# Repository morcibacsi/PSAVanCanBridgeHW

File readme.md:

# PSA VAN-CAN protocol bridge (hardware)

### What is it ?
This is the hardware needed for my [PSA CAN protocol bridge][psacanbridge] and [PSA VAN-CAN protocol bridge][psavancanbridge] software.

It was designed using KiCad 7.0.6 as a standalone board with an ESP32-WROOM-32 MCU.

### v1.5

:warning: **IF YOU ARE USING THE BOARD AS A VAN-CAN BOARD THEN BE AWARE THAT THE VAN DATA LINES HAVE BEEN SWAPPED IN THIS VERSION COMPARED TO THE PREVIOUS ONES. DATA LINE IS ON PIN 6 AND DATAB LINE IS ON PIN 5. ON PREVIOUS VERSIONS IT WAS THE OTHER WAY AROUND. SO YOU NEED TO SWAP THOSE WIRES ON YOUR PATCH LEAD IF YOU ARE UPGRADING FROM A PREVIOUS VERSION.**

It won't damage the board or your car, it just won't work if you don't swap the wires.

### Custom SPI shield

To have the flexibility to use either a MCP2515 or a TSS463 I designed a small custom PCB which can be manufactured with castellated holes and can be soldered to the back of this board. This is how it looks like. The design files for this PCB can be found on its own [repository][vancanspishield].

#### VAN-CAN bridge

To use it as a VAN-CAN bridge without the need for a custom SPI shield with the TSS463 you need to close the jumper marked with red rectangle on the front (1). This way the ESP32 will write directly to the VAN bus. You also need to close the jumper marked with red rectangle on the back (2) of the board to 3V3 so the CAN transceiver uses 3.3V logic levels.

If you would like to use the SPI shield with the TSS463 the jumper marked with red rectangle on the back (2) must be closed to 5V.

#### CAN-CAN bridge

To use it as a CAN-CAN bridge you need to populate the SPI shield with a MCP2515 and the jumper marked with red rectangle on the back (2) must be closed to 5V.

### Programming the board

The board can be programmed using the ESP32's UART0 for which you need a USB to serial adapter like on the picture below (or a similar one). As the ESP32 is a 3.3V device you need to make sure that the adapter is also 3.3V compatible.
The pins needed for programming are marked with orange rectangles on the front of the board on the picture below. Depending on the adapter you have you might need to cross connect the TX and RX pins.

You need to hold the BOOT button and press the RESET button to enter programming mode. I usually keep holding the BOOT button until the programming starts. After programming is done you can press the RESET button to restart the board.

💡 **Make sure you don't connect 5V and 12V at the same time to the board**

### Schema

### PCB

### Assembly

The board was designed to be as compact as possible, so I suggest to send the manufacturing files to JLCPCB and order with assembly service. But in order to have a working board some soldering is also needed. You can find the necessary components in the next section.

I bought a [DS3231 real time clock module for Raspberry Pi][DS3231] and disassembled that and placed its parts to J1 and U2.

The board dimensions were designed to fit a [70 x 45 x 18mm case][enclosure].

### BOM

I listed only those which aren't populated by the assembly company.

|Designator|Value         |Package                                         |
|----------|------------|------------------------------------------------|
|U8        |ESP32-WROOM-32      |     |
|J1        |Coin battery for DS3231      |     |
|U2        |DS3231      |SOIC-16W_7.5x10.3mm_P1.27mm     |
|C7        |100uF       |Capacitor_THT:CP_Radial_D6.3mm_P2.50mm     |
|C10       |220uF       |Capacitor_THT:CP_Radial_D6.3mm_P2.50mm     |

The connector for the power and signal wires is a JST-XH6 2.54 mm

The full BOM is in the production folder as a csv.

[vancanspishield]: https://github.com/morcibacsi/VanCanSpiShield
[psacanbridge]: https://github.com/morcibacsi/PSACANBridge
[psavancanbridge]: https://github.com/morcibacsi/PSAVANCANBridge
[DS3231]: https://www.aliexpress.com/item/1005006116699524.html
[enclosure]: https://www.aliexpress.com/item/1005005467281776.html

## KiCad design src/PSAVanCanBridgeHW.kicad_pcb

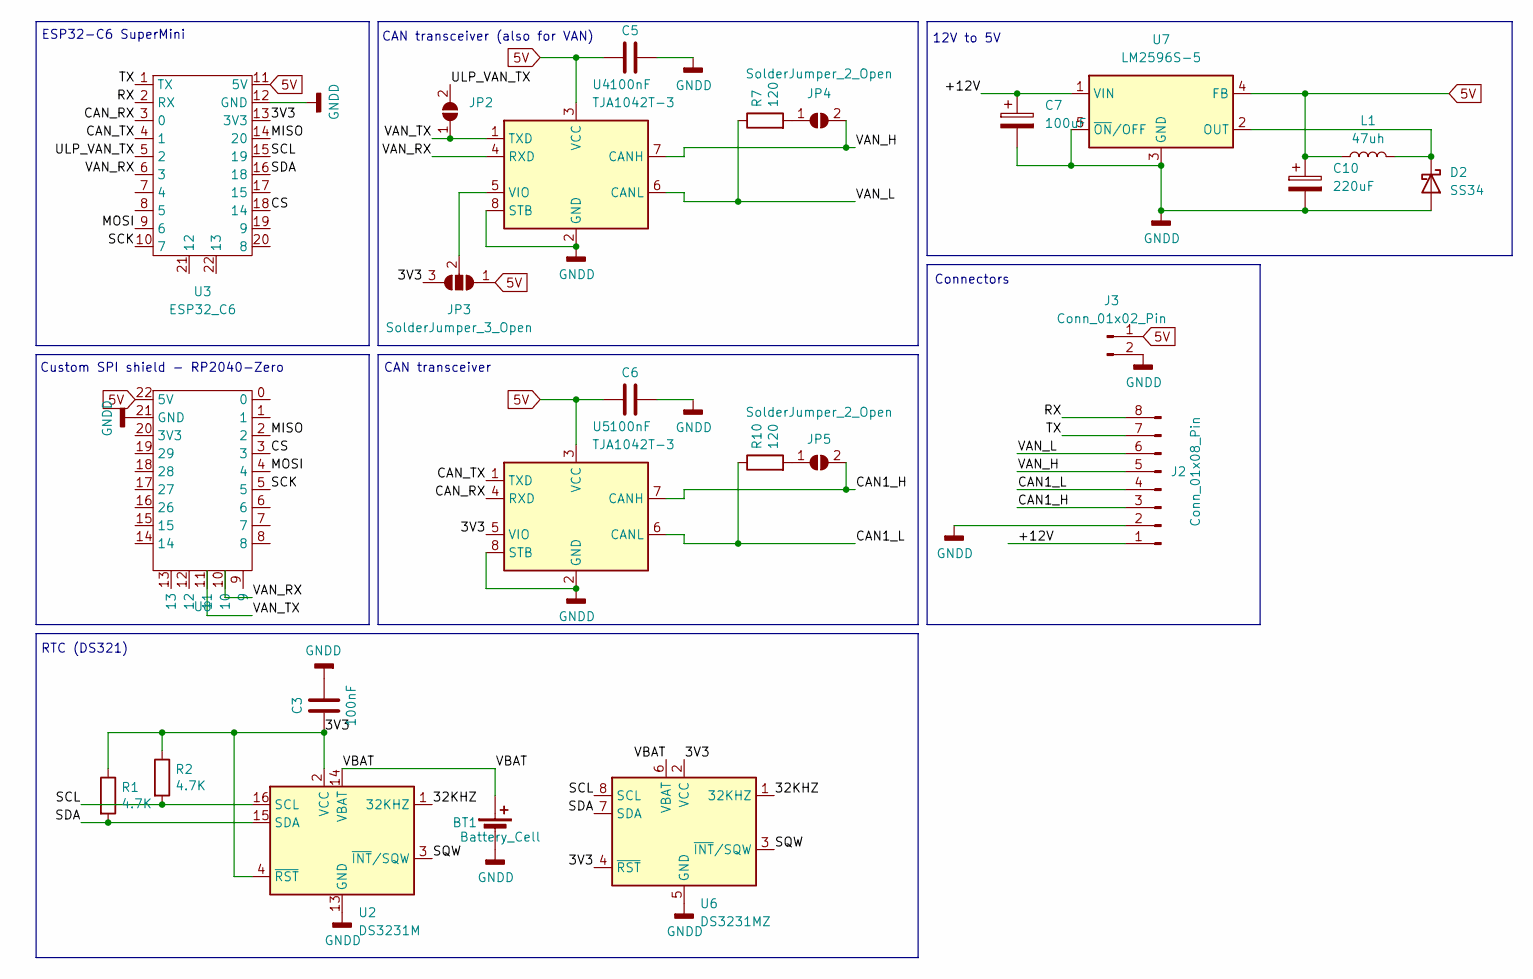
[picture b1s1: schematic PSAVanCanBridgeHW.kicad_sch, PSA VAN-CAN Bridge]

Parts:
BT1: Battery_Cell; BatteryHolder_Keystone_3000_1x12mm
C3, C5, C6: 100nF; C_0603_1608Metric_Pad1.08x0.95mm_HandSolder; MPN CC0603KRX7R9BB104; LCSC C14663
C7: 100uF; CP_Radial_D6.3mm_P2.50mm
C10: 220uF; CP_Radial_D6.3mm_P2.50mm
D2: SS34; D_SMA; MPN SS34; LCSC C7420365
J2: Conn_01x08_Pin; JST_EH_S8B-EH_1x08_P2.50mm_Horizontal
J3: Conn_01x02_Pin; PinHeader_1x02_P2.54mm_Vertical
JP2, JP4, JP5: SolderJumper_2_Open; SolderJumper-2_P1.3mm_Open_Pad1.0x1.5mm
JP3: SolderJumper_3_Open; SolderJumper-3_P1.3mm_Open_Pad1.0x1.5mm_NumberLabels
L1: 47uh; L_12x12mm_H8mm; MPN CDRH127NP-470MC; LCSC C167265
R1, R2: 4.7K; R_0603_1608Metric_Pad0.98x0.95mm_HandSolder; MPN 0603WAF4701T5E; LCSC C23162
R7, R10: 120; R_0603_1608Metric_Pad0.98x0.95mm_HandSolder; MPN 0603WAF1200T5E; LCSC C22787
U2: DS3231M; SOIC-16W_7.5x10.3mm_P1.27mm; JLCPCB Rotation Offset -90
U3: ESP32_C6; ESP32_c6_supermini
U4, U5: TJA1042T-3; SOIC-8_3.9x4.9mm_P1.27mm; MPN TJA1042T/3/1J; LCSC C132227
U6: DS3231MZ; SOIC-8_3.9x4.9mm_P1.27mm; MPN DS3231MZ+TRL; LCSC C37663
U7: LM2596S-5; TO-263-5_TabPin3; MPN LM2596S-5.0(UMW); LCSC C347421
U8: RP2040-Zero

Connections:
5V: C5.2, C6.2, C10.1, J3.1, JP3.1 (A), L1.1, U3.11 (5V), U4.3 (VCC), U5.3 (VCC), U7.4 (FB), U8.22 (5V)
/3V3: C3.2, JP3.3 (B), R1.1, R2.1, U2.2 (VCC), U2.4 (~RST), U3.13 (3V3), U5.5 (VIO), U6.2 (VCC), U6.4 (~RST)
/32KHZ: U2.1 (32KHZ), U6.1 (32KHZ)
/+12V: C7.1, J2.1, U7.1 (VIN)
/CAN1_H: J2.3, JP5.2 (B), U5.7 (CANH)
/CAN1_L: J2.4, R10.1, U5.6 (CANL)
/CAN_RX: U3.3 (0), U5.4 (RXD)
/CAN_TX: U3.4 (1), U5.1 (TXD)
/CS: U3.18 (14), U8.3
/MISO: U3.14 (20), U8.2
/MOSI: U3.9 (6), U8.4
/RX: J2.8, U3.2 (RX)
/SCK: U3.10 (7), U8.5
/SCL: R2.2, U2.16 (SCL), U3.15 (19), U6.8 (SCL)
/SDA: R1.2, U2.15 (SDA), U3.16 (18), U6.7 (SDA)
/SQW: U2.3 (~INT/SQW), U6.3 (~INT/SQW)
/TX: J2.7, U3.1 (TX)
/ULP_VAN_TX: JP2.2 (B), U3.5 (2)
/VAN_H: J2.5, JP4.2 (B), U4.7 (CANH)
/VAN_L: J2.6, R7.1, U4.6 (CANL)
/VAN_RX: U3.6 (3), U4.4 (RXD), U8.10
/VAN_TX: JP2.1 (A), U4.1 (TXD), U8.11
/VBAT: BT1.1 (+), U2.14 (VBAT), U6.6 (VBAT)
GNDD: BT1.2 (-), C3.1, C5.1, C6.1, C7.2, C10.2, D2.2 (A), J2.2, J3.2, U2.5 (GND), U2.6 (GND), U2.7 (GND), U2.8 (GND), U2.9 (GND), U2.10 (GND), U2.11 (GND), U2.12 (GND), U2.13 (GND), U3.12 (GND), U4.2 (GND), U4.8 (STB), U5.2 (GND), U5.8 (STB), U6.5 (GND), U7.3 (GND), U7.5 (~ON/OFF), U8.21 (GND)
unnamed: D2.1 (K), L1.2, U7.2 (OUT)
unnamed: JP3.2 (C), U4.5 (VIO)
unnamed: JP4.1 (A), R7.2
unnamed: JP5.1 (A), R10.2

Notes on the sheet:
RTC (DS321)
Connectors
Custom SPI shield - RP2040-Zero
CAN transceiver
12V to 5V
ESP32-C6 SuperMini
CAN transceiver (also for VAN)

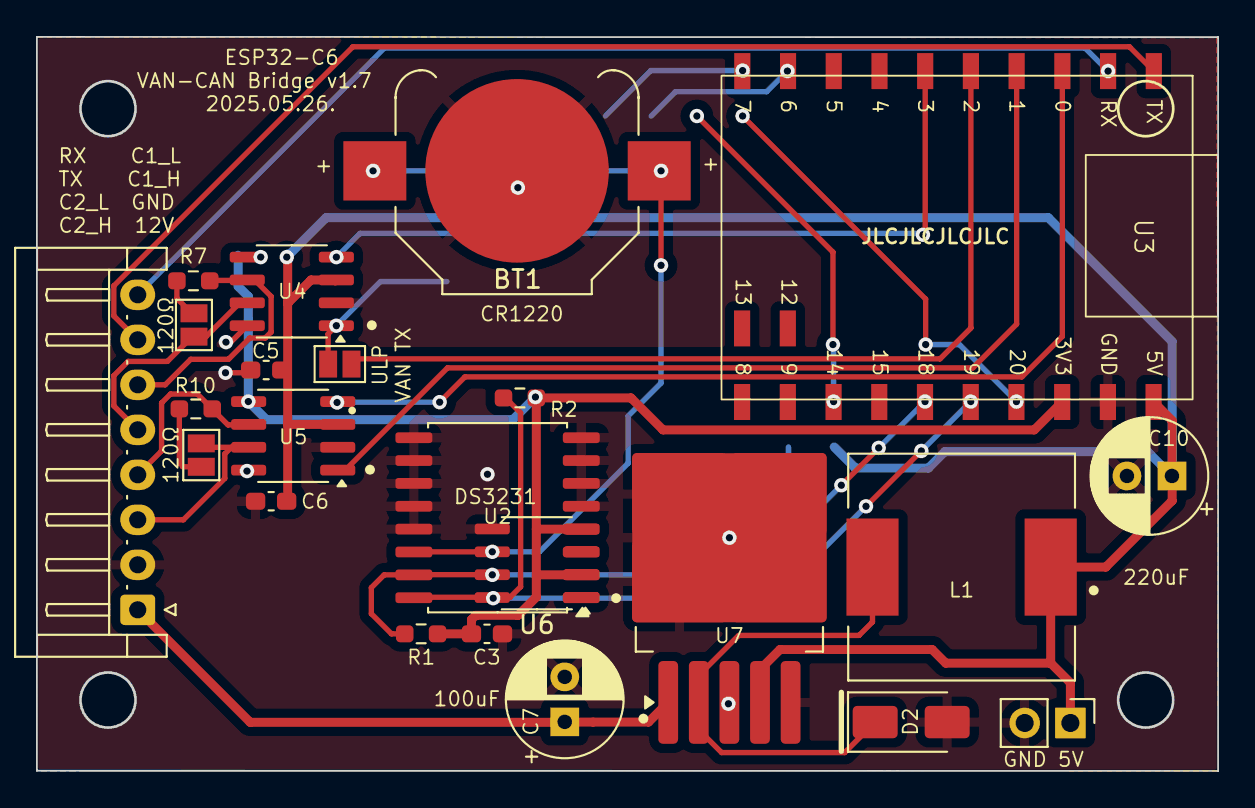
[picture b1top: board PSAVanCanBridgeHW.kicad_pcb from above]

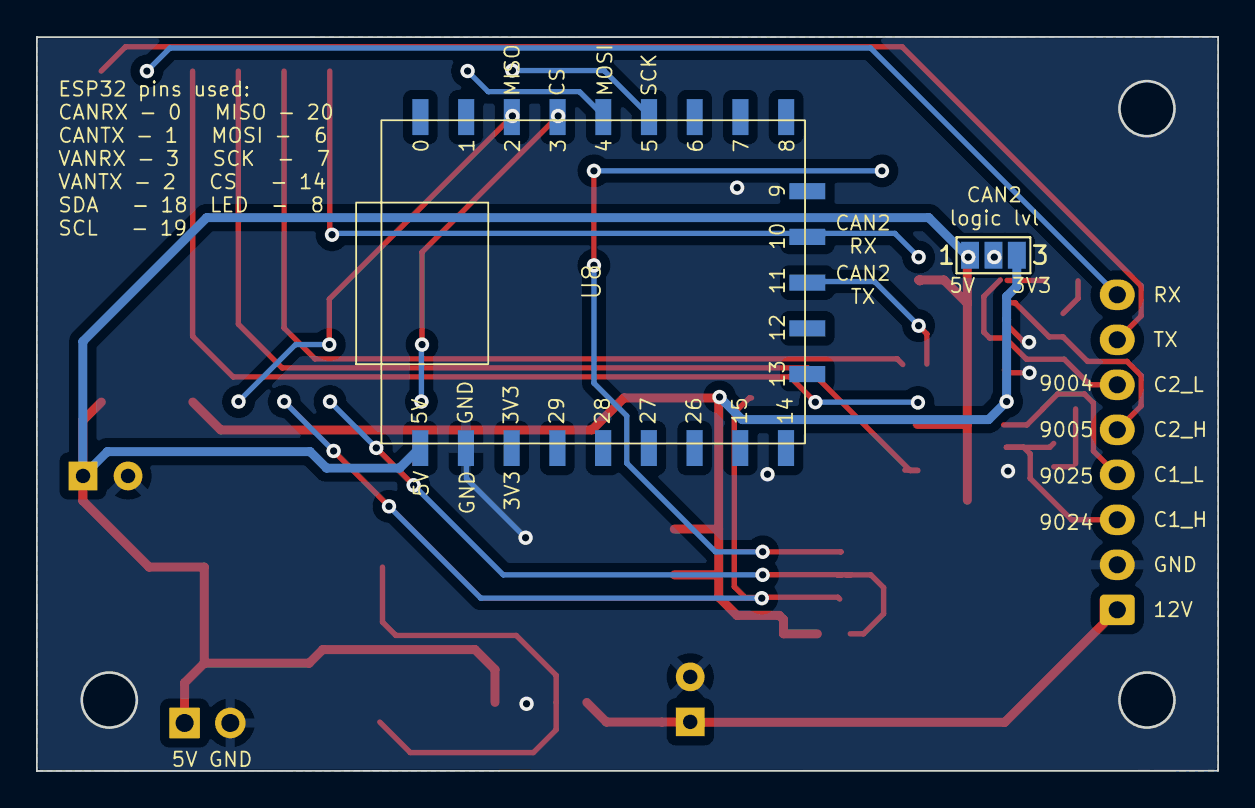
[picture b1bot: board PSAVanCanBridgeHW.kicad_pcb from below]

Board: 2 copper layers, 65.6 x 40.8 mm, 25 parts (2 on the bottom side), 28 nets.

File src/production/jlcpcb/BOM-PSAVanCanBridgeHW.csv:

Comment,Designator,Footprint,LCSC,Quantity
DS3231M,"U2",SOIC-16W_7.5x10.3mm_P1.27mm,C37663,2
DS3231MZ,"U6",SOIC-8_3.9x4.9mm_P1.27mm,C107410,2
TJA1042T-3,"U4,U5",SOIC-8_3.9x4.9mm_P1.27mm,C132227,2
100nF,"C3,C5,C6",C_0603_1608Metric_Pad1.08x0.95mm_HandSolder,C14663,3
47uh,L1,L_12x12mm_H8mm,C167265,1
120,"R10,R7",R_0603_1608Metric_Pad0.98x0.95mm_HandSolder,C22787,2
4.7K,"R1,R2",R_0603_1608Metric_Pad0.98x0.95mm_HandSolder,C23162,2
LM2596S-5,U7,TO-263-5_TabPin3,C347421,1
SS34,D2,D_SMA,C7420365,1
Conn_01x02_Pin,J3,PinHeader_1x02_P2.54mm_Vertical,,1
Battery_Cell,BT1,BatteryHolder_Keystone_3000_1x12mm,,1
220uF,C10,CP_Radial_D6.3mm_P2.50mm,,1
100uF,C7,CP_Radial_D6.3mm_P2.50mm,,1
Conn_01x08_Pin,J2,JST_EH_S8B-EH_1x08_P2.50mm_Horizontal,,1

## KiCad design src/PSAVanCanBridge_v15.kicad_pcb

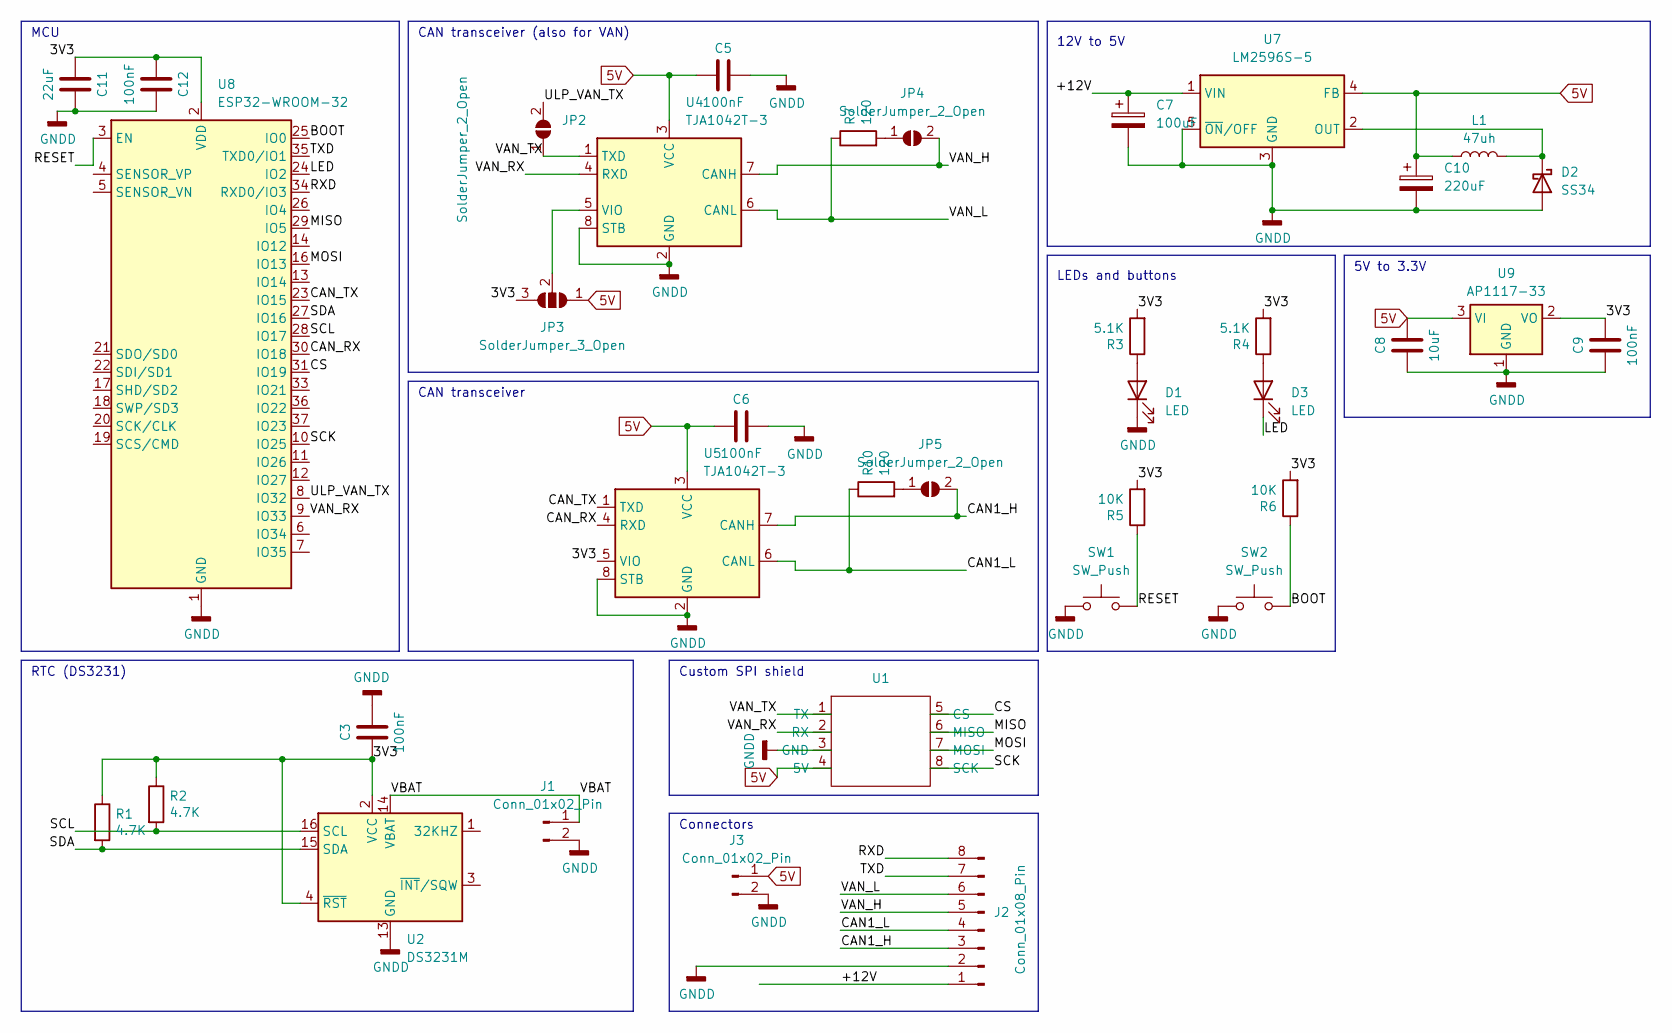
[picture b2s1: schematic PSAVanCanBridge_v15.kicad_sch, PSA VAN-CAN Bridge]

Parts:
C3, C5, C6, C12: 100nF; C_0603_1608Metric_Pad1.08x0.95mm_HandSolder; LCSC C14663
C7: 100uF; CP_Radial_D6.3mm_P2.50mm
C8: 10uF; C_0805_2012Metric_Pad1.18x1.45mm_HandSolder; LCSC C15850
C9: 100nF; C_0805_2012Metric_Pad1.18x1.45mm_HandSolder; LCSC C15850
C10: 220uF; CP_Radial_D6.3mm_P2.50mm
C11: 22uF; C_1206_3216Metric_Pad1.33x1.80mm_HandSolder; LCSC C478862
D1: LED; LED_0603_1608Metric_Pad1.05x0.95mm_HandSolder; LCSC C2286
D2: SS34; D_SMA; LCSC C7420365
D3: LED; LED_0805_2012Metric_Pad1.15x1.40mm_HandSolder; LCSC C2297
J1: Conn_01x02_Pin; DS3231_BatteryHolder
J2: Conn_01x08_Pin; JST_EH_S8B-EH_1x08_P2.50mm_Horizontal
J3: Conn_01x02_Pin; PinHeader_1x02_P2.54mm_Vertical
JP2, JP4, JP5: SolderJumper_2_Open; SolderJumper-2_P1.3mm_Open_Pad1.0x1.5mm
JP3: SolderJumper_3_Open; SolderJumper-3_P1.3mm_Open_Pad1.0x1.5mm_NumberLabels
L1: 47uh; L_12x12mm_H8mm; LCSC C167265
R1, R2: 4.7K; R_0603_1608Metric_Pad0.98x0.95mm_HandSolder; LCSC C25999
R3, R4: 5.1K; R_0603_1608Metric_Pad0.98x0.95mm_HandSolder; LCSC C473622
R5, R6: 10K; R_1206_3216Metric_Pad1.30x1.75mm_HandSolder; LCSC C431903
R7, R10: 120; R_0603_1608Metric_Pad0.98x0.95mm_HandSolder; LCSC C22787
SW1, SW2: SW_Push; SW_Push_1P1T_XKB_TS-1187A; LCSC C318884
U1: SPI_Shield
U2: DS3231M; SOIC-16W_7.5x10.3mm_P1.27mm; JLCPCB Rotation Offset -90
U4, U5: TJA1042T-3; SOIC-8_3.9x4.9mm_P1.27mm; LCSC C132227
U7: LM2596S-5; TO-263-5_TabPin3; LCSC C347421
U8: ESP32-WROOM-32
U9: AP1117-33; SOT-223-3_TabPin2; LCSC C6186

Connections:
5V: C5.2, C6.2, C8.1, C10.1, J3.1, JP3.1 (A), L1.1, U1.4 (5V), U4.3 (VCC), U5.3 (VCC), U7.4 (FB), U9.3 (VI)
/3V3: C3.2, C9.1, C11.2, C12.2, JP3.3 (B), R1.1, R2.1, R3.2, R4.2, R5.2, R6.2, U2.2 (VCC), U2.4 (~RST), U5.5 (VIO), U8.2 (VDD), U9.2 (VO)
/+12V: C7.1, J2.1, U7.1 (VIN)
/BOOT: R6.1, SW2.2, U8.25 (IO0)
/CAN1_H: J2.3, JP5.2 (B), U5.7 (CANH)
/CAN1_L: J2.4, R10.1, U5.6 (CANL)
/CAN_RX: U5.4 (RXD), U8.30 (IO18)
/CAN_TX: U5.1 (TXD), U8.23 (IO15)
/CS: U1.5 (CS), U8.31 (IO19)
/LED: D3.1 (K), U8.24 (IO2)
/MISO: U1.6 (MISO), U8.29 (IO5)
/MOSI: U1.7 (MOSI), U8.16 (IO13)
/RESET: R5.1, SW1.2, U8.3 (EN)
/RXD: J2.8, U8.34 (RXD0/IO3)
/SCK: U1.8 (SCK), U8.10 (IO25)
/SCL: R2.2, U2.16 (SCL), U8.28 (IO17)
/SDA: R1.2, U2.15 (SDA), U8.27 (IO16)
/TXD: J2.7, U8.35 (TXD0/IO1)
/ULP_VAN_TX: JP2.2 (B), U8.8 (IO32)
/VAN_H: J2.5, JP4.2 (B), U4.7 (CANH)
/VAN_L: J2.6, R7.1, U4.6 (CANL)
/VAN_RX: U1.2 (RX), U4.4 (RXD), U8.9 (IO33)
/VAN_TX: JP2.1 (A), U1.1 (TX), U4.1 (TXD)
/VBAT: J1.1, U2.14 (VBAT)
GNDD: C3.1, C5.1, C6.1, C7.2, C8.2, C9.2, C10.2, C11.1, C12.1, D1.1 (K), D2.2 (A), J1.2, J2.2, J3.2, SW1.1, SW2.1, U1.3 (GND), U2.5 (GND), U2.6 (GND), U2.7 (GND), U2.8 (GND), U2.9 (GND), U2.10 (GND), U2.11 (GND), U2.12 (GND), U2.13 (GND), U4.2 (GND), U4.8 (STB), U5.2 (GND), U5.8 (STB), U7.3 (GND), U7.5 (~ON/OFF), U8.1 (GND), U8.15 (GND), U8.38 (GND), U8.39 (GND), U9.1 (GND)
unnamed: D1.2 (A), R3.1
unnamed: D2.1 (K), L1.2, U7.2 (OUT)
unnamed: D3.2 (A), R4.1
unnamed: JP3.2 (C), U4.5 (VIO)
unnamed: JP4.1 (A), R7.2
unnamed: JP5.1 (A), R10.2

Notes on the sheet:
RTC (DS3231)
12V to 5V
Custom SPI shield
CAN transceiver (also for VAN)
LEDs and buttons
Connectors
5V to 3.3V
CAN transceiver
MCU

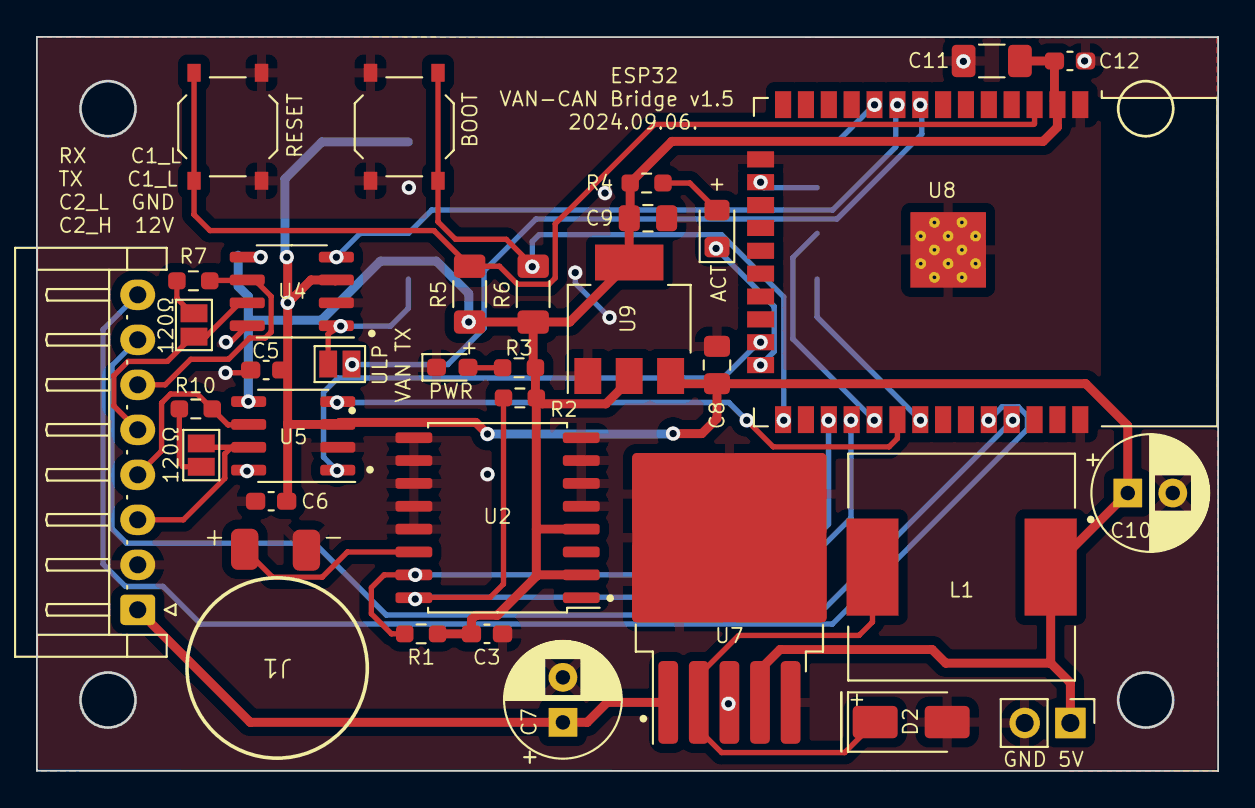
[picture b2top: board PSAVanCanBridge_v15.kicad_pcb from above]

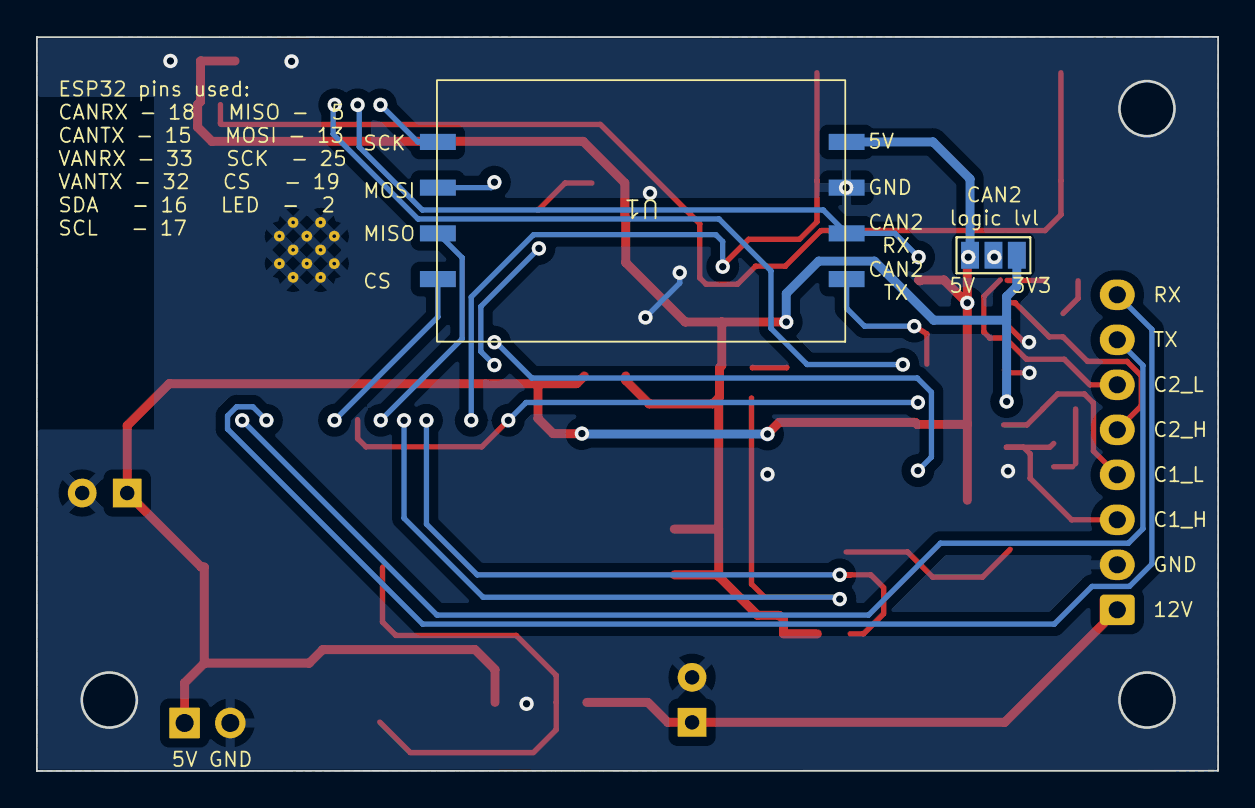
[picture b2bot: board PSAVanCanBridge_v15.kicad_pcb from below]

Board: 2 copper layers, 65.6 x 40.8 mm, 37 parts (2 on the bottom side), 31 nets.

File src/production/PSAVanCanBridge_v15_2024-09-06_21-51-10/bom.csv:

Designator,Footprint,Quantity,Value,LCSC Part #
C10,CP_Radial_D6.3mm_P2.50mm,1,220uF,
C11,1206,1,22uF,C478862
"C12, C3, C5, C6",0603,4,100nF,C14663
C7,CP_Radial_D6.3mm_P2.50mm,1,100uF,
C8,0805,1,10uF,C15850
C9,0805,1,100nF,C15850
D1,0603,1,LED,C2286
D2,D_SMA,1,SS34,C7420365
D3,0805,1,LED,C2297
J1,DS3231_BatteryHolder,1,Conn_01x02_Pin,
J2,JST_EH_S8B-EH_1x08_P2.50mm_Horizontal,1,Conn_01x08_Pin,
J3,PinHeader_1x02_P2.54mm_Vertical,1,Conn_01x02_Pin,
"JP2, JP4, JP5",SolderJumper-2_P1.3mm_Open_Pad1.0x1.5mm,3,SolderJumper_2_Open,
JP3,SolderJumper-3_P1.3mm_Open_Pad1.0x1.5mm_NumberLabels,1,SolderJumper_3_Open,
L1,L_12x12mm_H8mm,1,47uh,C167265
"R1, R2",0603,2,4.7K,C25999
"R10, R7",0603,2,120,
"R3, R4",0603,2,5.1K,C473622
"R5, R6",1206,2,10K,C431903
"SW1, SW2",SW_Push_1P1T_XKB_TS-1187A,2,SW_Push,C318884
U1,SPI_Shield,1,~,
U2,SOIC-16W_7.5x10.3mm_P1.27mm,1,DS3231M,
"U4, U5",SOIC-8_3.9x4.9mm_P1.27mm,2,TJA1042T-3,C132227
U7,TO-263-5_TabPin3,1,LM2596S-5,C347421
U8,ESP32-WROOM-32,1,ESP32-WROOM-32,
U9,SOT-223-3_TabPin2,1,AP1117-33,C6186

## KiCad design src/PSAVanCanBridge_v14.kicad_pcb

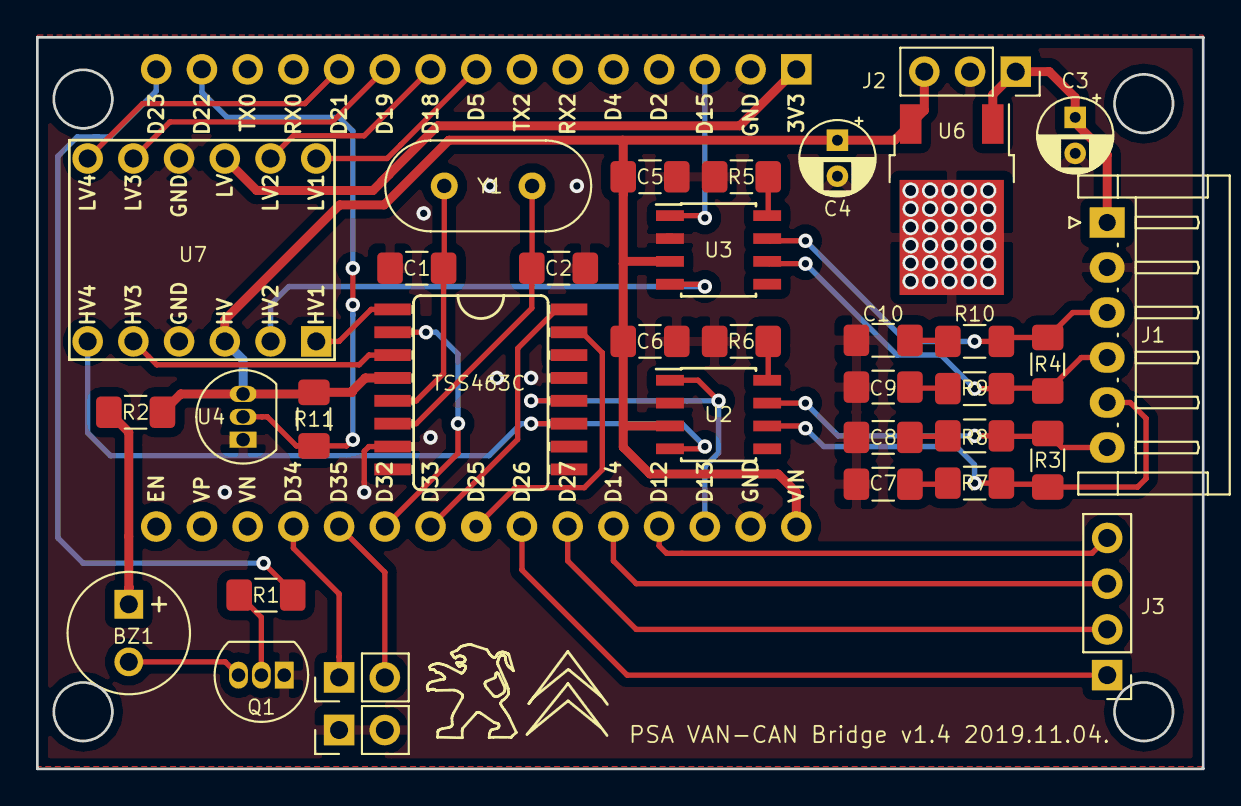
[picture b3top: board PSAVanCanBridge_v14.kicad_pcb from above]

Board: 2 copper layers, 64.8 x 40.6 mm, 36 parts (0 on the bottom side), 40 nets.

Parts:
BZ1: Buzzer; MagneticBuzzer_Kingstate_KCG0601
C1, C2: 22pF; C_1206_3216Metric_Pad1.42x1.75mm_HandSolder
C3: 0.33uF; CP_Radial_D4.0mm_P2.00mm
C4: 0.1uF; CP_Radial_D4.0mm_P2.00mm
C5, C6: 0.1uF; C_1206_3216Metric_Pad1.42x1.75mm_HandSolder
C7, C8, C9, C10: 560pF; C_1206_3216Metric_Pad1.42x1.75mm_HandSolder
J1: Conn_01x06_Male; JST_EH_S06B-EH_1x06_P2.50mm_Horizontal
J2: Conn_01x03_Male; PinSocket_1x03_P2.54mm_Vertical
J3: Conn_01x04_Male; PinHeader_1x04_P2.54mm_Vertical
J4, J5: Conn_01x02_Male; PinHeader_1x02_P2.54mm_Vertical
Q1: PN2222A; TO-92_Inline
R1, R2: 2.2K; R_1206_3216Metric_Pad1.42x1.75mm_HandSolder
R3, R4: 120; R_1206_3216Metric_Pad1.42x1.75mm_HandSolder
R5, R6, R11: 4.7K; R_1206_3216Metric_Pad1.42x1.75mm_HandSolder
R7, R8, R9, R10: 100; R_1206_3216Metric_Pad1.42x1.75mm_HandSolder
U1: TSS463C; SO16L
U2, U3: MCP2551-I-SN; SOIC-8_3.9x4.9mm_P1.27mm
U4: DS18B20; TO-92_Inline
U5: ESP32; ESP32_shield
U6: LM7805_TO220; TO-252-2
U7: LevelShifter4Shield; LevelShifter4_shield
Y1: 8MHz; Crystal_HC49-4H_Vertical

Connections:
5V: C4.1, C5.2, C6.2, J2.3, R2.2, R11.1, U1.4, U2.3, U3.3, U4.3, U5.15, U6.3, U7.9
/3V3: U5.30, U7.3
/+12V: C3.1, J1.1, J2.1, U6.1
/BZ: R1.2, U5.16
/CANH: J1.3, R4.1, R10.1, U3.7
/CANL: J1.4, R4.2, R9.1, U3.6
/CAN_RX: U3.4, U7.8
/CAN_TX: U3.1, U5.28
/CS_VAN: U1.2, U5.6
/DATA: J1.5, R3.2, R7.1, U2.6
/DATAB: J1.6, R3.1, R8.1, U2.7
/IRQ: U1.3, U7.11
/MISO: U1.1, U7.7
/MOSI: U1.16, U5.7
/SCK: U1.15, U5.8
/Temp: R11.2, U4.2, U5.17
/VAN_RX: U1.11, U2.4, U7.12
/VAN_TX: U1.12, U2.1, U5.13
GNDD: C1.2, C2.2, C3.2, C4.2, C5.1, C6.1, C7.1, C8.1, C9.1, C10.1, J1.2, J2.2, J5.1, J5.2, Q1.1, R5.2, R6.2, U1.7, U1.13, U2.2, U3.2, U4.1, U5.14, U5.29, U6.2, U7.4, U7.10
unnamed: BZ1.1, R2.1
unnamed: BZ1.2, Q1.3
unnamed: C1.1, U1.5, Y1.1
unnamed: C2.1, U1.6, Y1.2
unnamed: C7.2, R7.2
unnamed: C8.2, R8.2
unnamed: C9.2, R9.2
unnamed: C10.2, R10.2
unnamed: J3.1, U5.9
unnamed: J3.2, U5.10
unnamed: J3.3, U5.11
unnamed: J3.4, U5.12
unnamed: J4.1, U5.4
unnamed: J4.2, U5.5
unnamed: Q1.2, R1.1
unnamed: R5.1, U3.8
unnamed: R6.1, U2.8
unnamed: U5.20, U7.6
unnamed: U5.21, U7.5
unnamed: U5.22, U7.2
unnamed: U5.23, U7.1

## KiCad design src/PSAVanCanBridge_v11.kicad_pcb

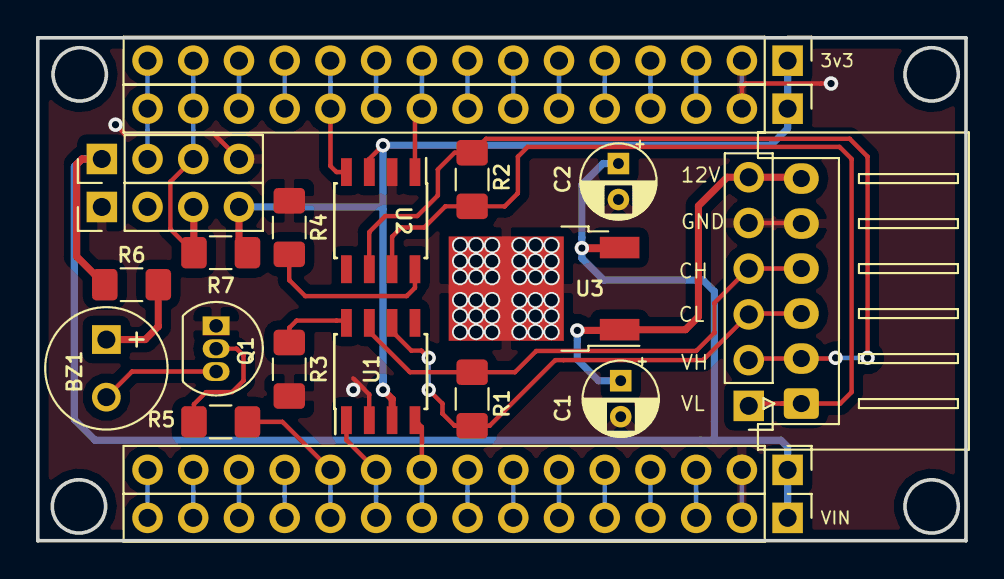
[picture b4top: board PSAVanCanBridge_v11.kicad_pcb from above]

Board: 2 copper layers, 51.6 x 27.9 mm, 22 parts (0 on the bottom side), 39 nets.

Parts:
BZ1: Buzzer; MagneticBuzzer_Kingstate_KCG0601
C1: 0.33 uF; CP_Radial_D4.0mm_P2.00mm
C2: 0.1 uF; CP_Radial_D4.0mm_P2.00mm
J1, J7: Row1; PinHeader_1x15_P2.54mm_Vertical
J2, J8: Row2; PinHeader_1x15_P2.54mm_Vertical
J3: Conn_01x06_Male; JST_XH_S06B-XH-A_1x06_P2.50mm_Horizontal
J4: Conn_01x06_Male; PinHeader_1x06_P2.54mm_Vertical
J5, J10: Conn_01x04_Female; PinHeader_1x04_P2.54mm_Vertical
Q1: PN2222A; TO-92_Inline
R1, R2: 120; R_1206_3216Metric_Pad1.42x1.75mm_HandSolder
R3, R4: 10K; R_1206_3216Metric_Pad1.42x1.75mm_HandSolder
R5: 2.2K (470/220 for IR); R_1206_3216Metric_Pad1.42x1.75mm_HandSolder
R6: 2.2K; R_1206_3216Metric_Pad1.42x1.75mm_HandSolder
R7: 4.7K; R_1206_3216Metric_Pad1.42x1.75mm_HandSolder
U1, U2: SN65HVD230; SOIC-8_3.9x4.9mm_P1.27mm
U3: LM78M05_TO220; TO-252-2

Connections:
3V3: J1.1, J5.4, J7.1, R7.1, U1.3, U2.3
5V: C2.1, J2.1, J8.1, J10.1, R6.2, U3.3
D4: J1.5, J7.5
D5: J1.8, J7.8
D12: J2.4, J8.4
D13: J2.3, J8.3
D18: J1.9, J7.9, U2.1
D19: J1.10, J7.10
D21: J1.11, J7.11, U2.4
D22: J1.14, J5.3, J7.14, J10.3, R7.2
D25: J2.8, J8.8
D32: J2.10, J8.10, U1.1
D33: J2.9, J8.9, U1.4
D34: J2.12, J8.12
D35: J2.11, J8.11, R5.2
GND: C1.2, C2.2, J1.2, J2.2, J3.5, J4.5, J5.1, J7.2, J8.2, J10.4, Q1.1, R3.2, R4.2, U1.2, U2.2, U3.2
unnamed: BZ1.1, R6.1
unnamed: BZ1.2, Q1.3
unnamed: C1.1, J3.6, J4.6, U3.1
unnamed: J1.3, J7.3
unnamed: J1.4, J7.4
unnamed: J1.6, J7.6
unnamed: J1.7, J7.7
unnamed: J1.15, J7.15, J10.2
unnamed: J2.5, J8.5
unnamed: J2.6, J8.6
unnamed: J2.7, J8.7
unnamed: J2.13, J8.13
unnamed: J2.14, J8.14
unnamed: J2.15, J8.15
unnamed: J3.1, J4.1, R2.1, U2.7
unnamed: J3.2, J4.2, R2.2, U2.6
unnamed: J3.3, J4.3, R1.1, U1.6
unnamed: J3.4, J4.4, R1.2, U1.7
unnamed: Q1.2, R5.1
unnamed: R3.1, U1.8
unnamed: R4.1, U2.8
RX0: J1.12, J7.12
TX0: J1.13, J7.13

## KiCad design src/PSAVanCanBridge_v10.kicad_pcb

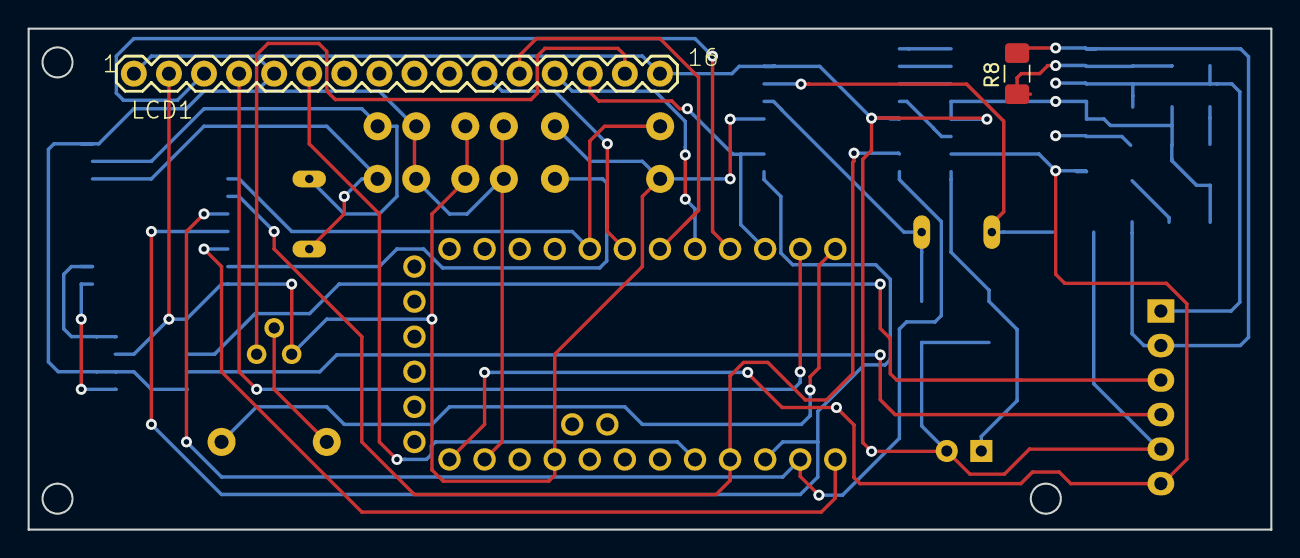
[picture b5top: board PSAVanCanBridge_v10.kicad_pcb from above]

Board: 2 copper layers, 90.0 x 36.3 mm, 29 parts (0 on the bottom side), 38 nets.

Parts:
C1, C4: .1uF; CAP-PTH-SMALL-KIT
C2, C3: 22pf; CAP-PTH-SMALL-KIT
C9, C13: 330pF; C_1206_3216Metric_Pad1.42x1.75mm_HandSolder
C10: 10nF; C_1206_3216Metric_Pad1.42x1.75mm_HandSolder
C11, C12: 22pf; C_1206_3216Metric_Pad1.42x1.75mm_HandSolder
C14: 15uF; CP_Radial_D8.0mm_P2.50mm
C15: 100nF; C_1206_3216Metric_Pad1.42x1.75mm_HandSolder
IC1: MCP2515-E_SO; SO18L
J2: Conn_01x06_Female; JST_XH_S06B-XH-A-1_1x06_P2.50mm_Horizontal
LCD1: M16PTH; 1X16
MTC1: MTC-30521; SO16L
Q1: 20Mhz; QS
Q2: 2N3906; TO92
R1, R3: 10K; AXIAL-0.3-KIT
R2: 220; AXIAL-0.3-KIT
R6, R7: 51; R_1206_3216Metric_Pad1.42x1.75mm_HandSolder
R8, R9: 4.3K; R_1206_3216Metric_Pad1.42x1.75mm_HandSolder
R10: 10K; R_1206_3216Metric_Pad1.42x1.75mm_HandSolder
TSS1: TSS463C; SO16L
U1: MCP2551; SO08
U$2: ARDUINO_PRO_MINI
VQ2: 8Mhz; QS

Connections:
/+12V: J2.6, MTC1.8, MTC1.10, U$2.RAW
/CANH: J2.4, U1.7
/CANL: J2.3, U1.6
/CS_VAN: LCD1.14, TSS1.2, U$2.D7
/DATA: J2.2, MTC1.1, R6.1, R8.1
/DATAB: J2.1, MTC1.3, R7.1, R9.1
/DB4: LCD1.11, U$2.D3
/DB5: LCD1.12, U$2.D4
/DB6: LCD1.13, U$2.D5
/E: LCD1.6, U$2.A0
/LED+: LCD1.15, Q2.1
/MISO: IC1.15, TSS1.1, U$2.D12
/MOSI: IC1.14, TSS1.16, U$2.D11
/RS: LCD1.4, U$2.D8
/SCLK: IC1.13, TSS1.15, U$2.D13
/VAN-RX0: MTC1.14, TSS1.11
/VAN-RX1: MTC1.16, TSS1.9
/VAN-RX2: MTC1.15, TSS1.10
/VAN-TX: MTC1.11, TSS1.12
/VO: LCD1.3, U$2.D6
GND: C1.2, C2.2, C3.2, C4.2, C9.1, C10.1, C11.1, C12.1, C13.2, C14.2, C15.2, IC1.9, J2.5, LCD1.1, LCD1.5, LCD1.16, MTC1.4, MTC1.5, MTC1.12, MTC1.13, R10.2, TSS1.7, TSS1.13, U1.2, U1.8, U$2.GND1
unnamed: C2.1, IC1.8, Q1.2
unnamed: C3.1, IC1.7, Q1.1
unnamed: C9.2, R6.2
unnamed: C10.2, MTC1.2, R8.2, R9.2
unnamed: C11.2, TSS1.5, VQ2.2
unnamed: C12.2, TSS1.6, VQ2.1
unnamed: C13.1, R7.2
unnamed: C14.1, C15.1, MTC1.9
unnamed: IC1.1, U1.1
unnamed: IC1.2, U1.4
unnamed: IC1.12, R3.P$2, U$2.D2
unnamed: IC1.16, U$2.D10
unnamed: IC1.17, R1.P$1
unnamed: MTC1.6, R10.1
unnamed: Q2.2, R2.P$2
unnamed: R2.P$1, U$2.D9
VCC: C1.1, C4.1, IC1.18, LCD1.2, Q2.3, R1.P$2, R3.P$1, TSS1.4, U1.3, U$2.VCC1

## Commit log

2019-12-07 Added files
2019-12-07 Added readme.md
2019-12-22 Updated photos
2019-12-22 Updated photo
2021-08-27 Fixed value of R5/R6 in the BOM of the full board
2023-11-14 First version of 3D printed case
2025-10-12 Added picture for firmware upload connection
